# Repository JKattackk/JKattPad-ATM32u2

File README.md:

# JKattPad-ATM32u2
Custom numpad using ATMega32u2, QMK, and USB-C connectivity

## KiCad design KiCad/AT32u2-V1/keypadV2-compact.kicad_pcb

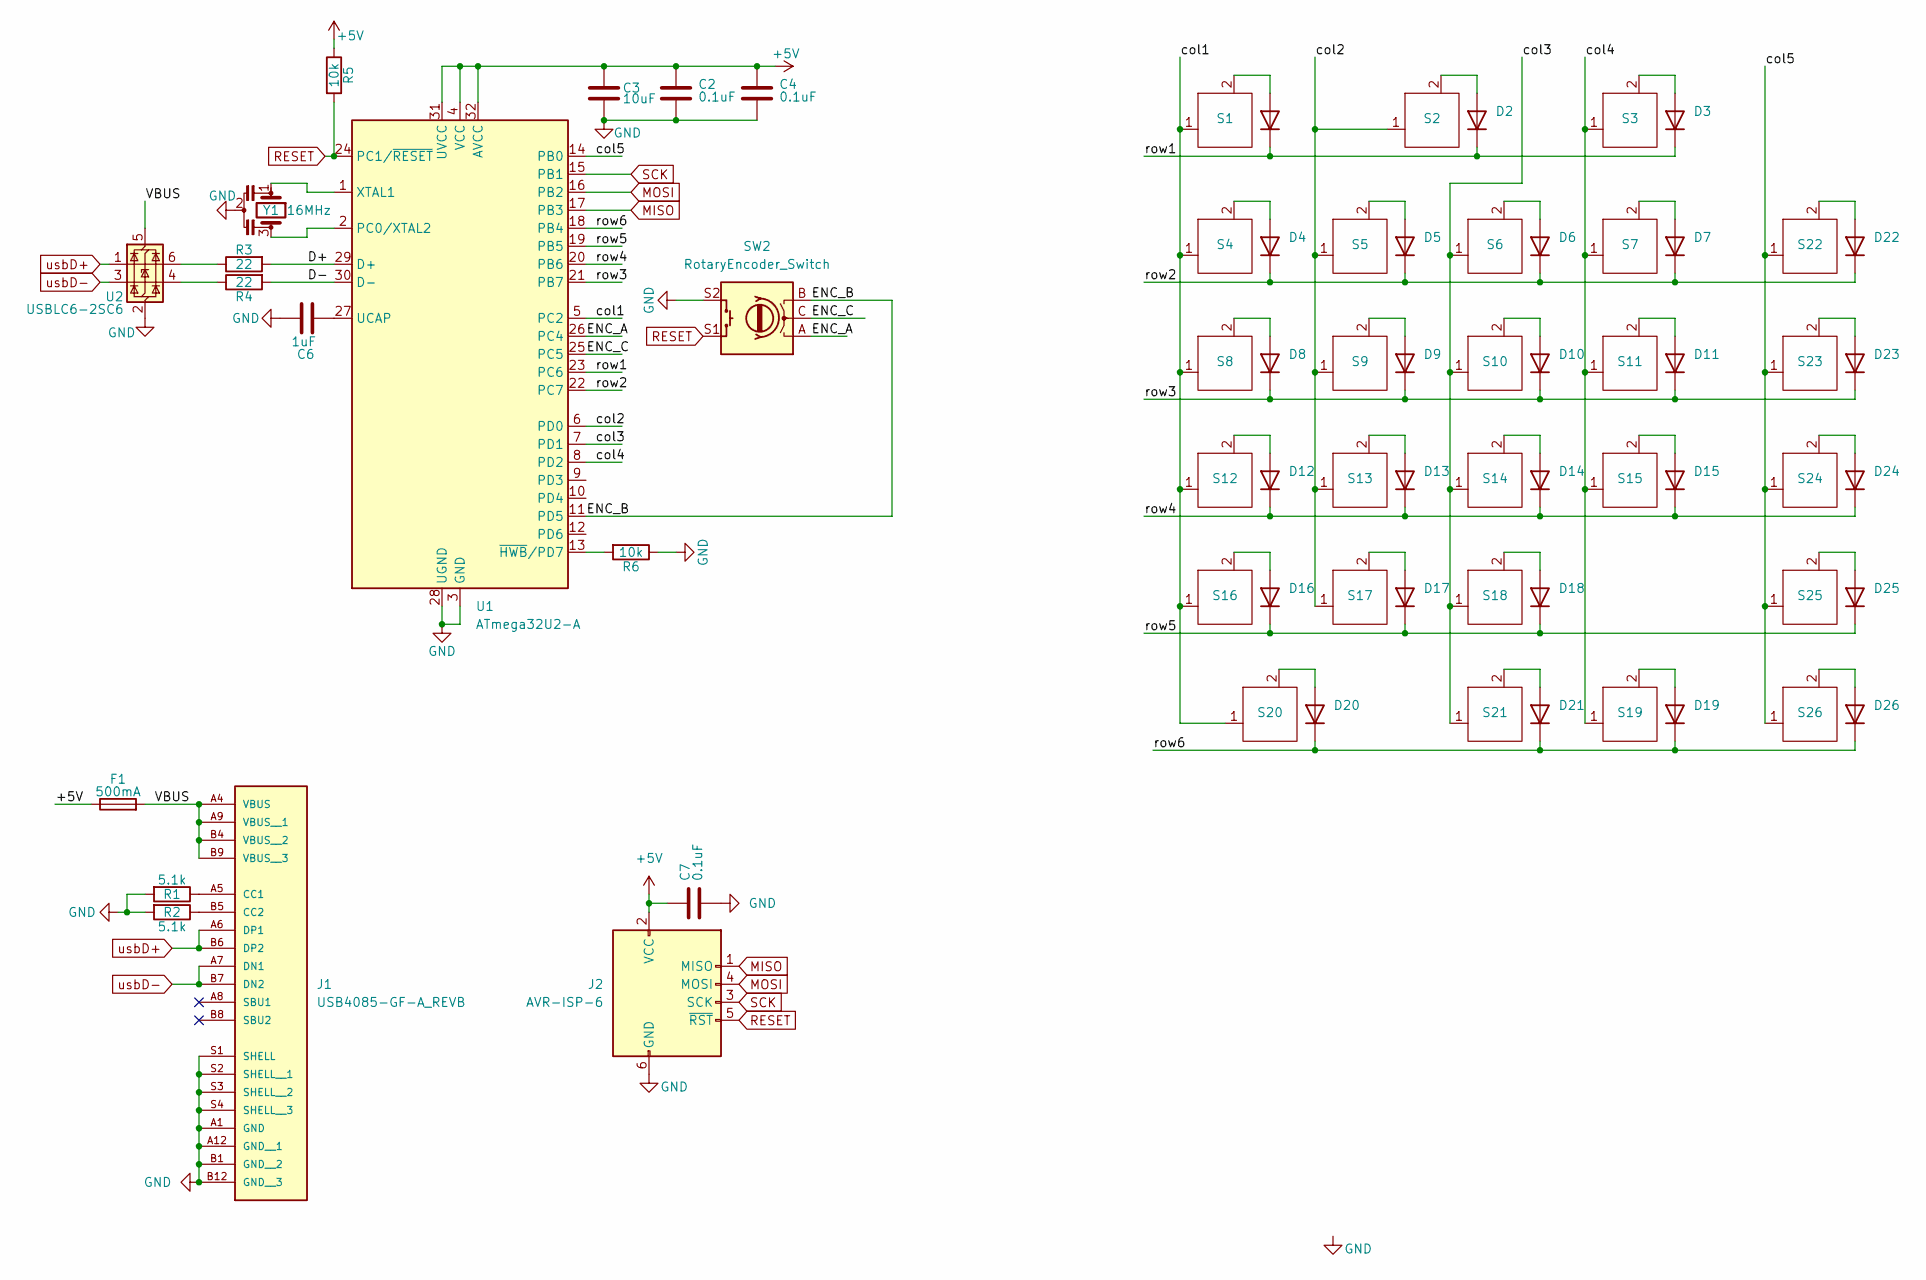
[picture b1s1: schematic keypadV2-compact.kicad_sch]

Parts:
C2, C4, C7: 0.1uF; C_0805_2012Metric_Pad1.18x1.45mm_HandSolder
C3: 10uF; C_0805_2012Metric_Pad1.18x1.45mm_HandSolder
C6: 1uF; C_0805_2012Metric_Pad1.18x1.45mm_HandSolder
D1, D2, D3, D4, D5, D6, D7, D8, D9, D10, D11, D12, D13, D14, D15, D16, D17, D18, D19, D20, D21, D22, D23, D24, D25, D26: BAV16W; D_SOD-123
F1: 500mA; Fuse_0805_2012Metric_Pad1.15x1.40mm_HandSolder
J1: USB4085-GF-A_REVB; GCT_USB4085-GF-A_REVB; PARTREV B
J2: AVR-ISP-6; PinHeader_2x03_P2.54mm_Vertical
R1, R2: 5.1k; R_0805_2012Metric_Pad1.20x1.40mm_HandSolder
R3, R4: 22; R_0805_2012Metric_Pad1.20x1.40mm_HandSolder
R5, R6: 10k; R_0805_2012Metric_Pad1.20x1.40mm_HandSolder
S1, S3, S4, S5, S6, S7, S8, S9, S10, S11, S12, S13, S14, S15, S16, S17, S18, S21, S22, S23, S24, S25, S26: MX-Alps-Hybrid-1U
S2, S20: MX-Alps-Hybrid-2U-nostab
S19: MX-Alps-Hybrid-2U-Vertical-nostab
SW2: RotaryEncoder_Switch; RotaryEncoder_Alps_EC11E-Switch_Vertical_H20mm
U1: ATmega32U2-A; TQFP-32_7x7mm_P0.8mm
U2: USBLC6-2SC6; SOT-23-6_Handsoldering
Y1: 16MHz; Resonator_SMD_Murata_CSTxExxV-3Pin_3.0x1.1mm_HandSoldering

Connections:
+5V: C2.1, C3.1, C4.1, C7.1, F1.1, J2.2 (VCC), R5.1, U1.4 (VCC), U1.31 (UVCC), U1.32 (AVCC)
/D+: R3.2, U1.29 (D+)
/D-: R4.2, U1.30 (D-)
/ENC_A: SW2.A, U1.26 (PC4)
/ENC_B: SW2.B, U1.11 (PD5)
/ENC_C: SW2.C, U1.25 (PC5)
/VBUS: F1.2, J1.A4 (VBUS), J1.A9 (VBUS__1), J1.B4 (VBUS__2), J1.B9 (VBUS__3), U2.5 (VBUS)
/col1: S1.1, S4.1, S8.1, S12.1, S16.1, S20.1, U1.5 (PC2)
/col2: S2.1, S5.1, S9.1, S13.1, S17.1, U1.6 (PD0)
/col3: S6.1, S10.1, S14.1, S18.1, S21.1, U1.7 (PD1)
/col4: S3.1, S7.1, S11.1, S15.1, S19.1, U1.8 (PD2)
/col5: S22.1, S23.1, S24.1, S25.1, S26.1, U1.14 (PB0)
/row1: D1.1 (K), D2.1 (K), D3.1 (K), U1.23 (PC6)
/row2: D4.1 (K), D5.1 (K), D6.1 (K), D7.1 (K), D22.1 (K), U1.22 (PC7)
/row3: D8.1 (K), D9.1 (K), D10.1 (K), D11.1 (K), D23.1 (K), U1.21 (PB7)
/row4: D12.1 (K), D13.1 (K), D14.1 (K), D15.1 (K), D24.1 (K), U1.20 (PB6)
/row5: D16.1 (K), D17.1 (K), D18.1 (K), D25.1 (K), U1.19 (PB5)
/row6: D19.1 (K), D20.1 (K), D21.1 (K), D26.1 (K), U1.18 (PB4)
GND: C2.2, C3.2, C4.2, C6.2, C7.2, J1.A1 (GND), J1.A12 (GND__1), J1.B1 (GND__2), J1.B12 (GND__3), J1.S1 (SHELL), J1.S2 (SHELL__1), J1.S3 (SHELL__2), J1.S4 (SHELL__3), J2.6 (GND), R1.2, R2.2, R6.1, SW2.S2, U1.3 (GND), U1.28 (UGND), U2.2 (GND), Y1.2
MISO: J2.1 (MISO), U1.17 (PB3)
MOSI: J2.4 (MOSI), U1.16 (PB2)
unnamed: D1.2 (A), S1.2
unnamed: D2.2 (A), S2.2
unnamed: D3.2 (A), S3.2
unnamed: D4.2 (A), S4.2
unnamed: D5.2 (A), S5.2
unnamed: D6.2 (A), S6.2
unnamed: D7.2 (A), S7.2
unnamed: D8.2 (A), S8.2
unnamed: D9.2 (A), S9.2
unnamed: D10.2 (A), S10.2
unnamed: D11.2 (A), S11.2
unnamed: D12.2 (A), S12.2
unnamed: D13.2 (A), S13.2
unnamed: D14.2 (A), S14.2
unnamed: D15.2 (A), S15.2
unnamed: D16.2 (A), S16.2
unnamed: D17.2 (A), S17.2
unnamed: D18.2 (A), S18.2
unnamed: D19.2 (A), S19.2
unnamed: D20.2 (A), S20.2
unnamed: D21.2 (A), S21.2
unnamed: D22.2 (A), S22.2
unnamed: D23.2 (A), S23.2
unnamed: D24.2 (A), S24.2
unnamed: D25.2 (A), S25.2
unnamed: D26.2 (A), S26.2
unnamed: J1.A5 (CC1), R1.1
unnamed: J1.B5 (CC2), R2.1
unnamed: R3.1, U2.6 (I/O1)
unnamed: R4.1, U2.4 (I/O2)
unnamed: U1.2 (PC0/XTAL2), Y1.3
unnamed: C6.1, U1.27 (UCAP)
unnamed: U1.1 (XTAL1), Y1.1
unnamed: R6.2, U1.13 (~HWB/PD7)
RESET: J2.5 (~RST), R5.2, SW2.S1, U1.24 (PC1/~RESET)
SCK: J2.3 (SCK), U1.15 (PB1)
usbD+: J1.A6 (DP1), J1.B6 (DP2), U2.1 (I/O1)
usbD-: J1.A7 (DN1), J1.B7 (DN2), U2.3 (I/O2)

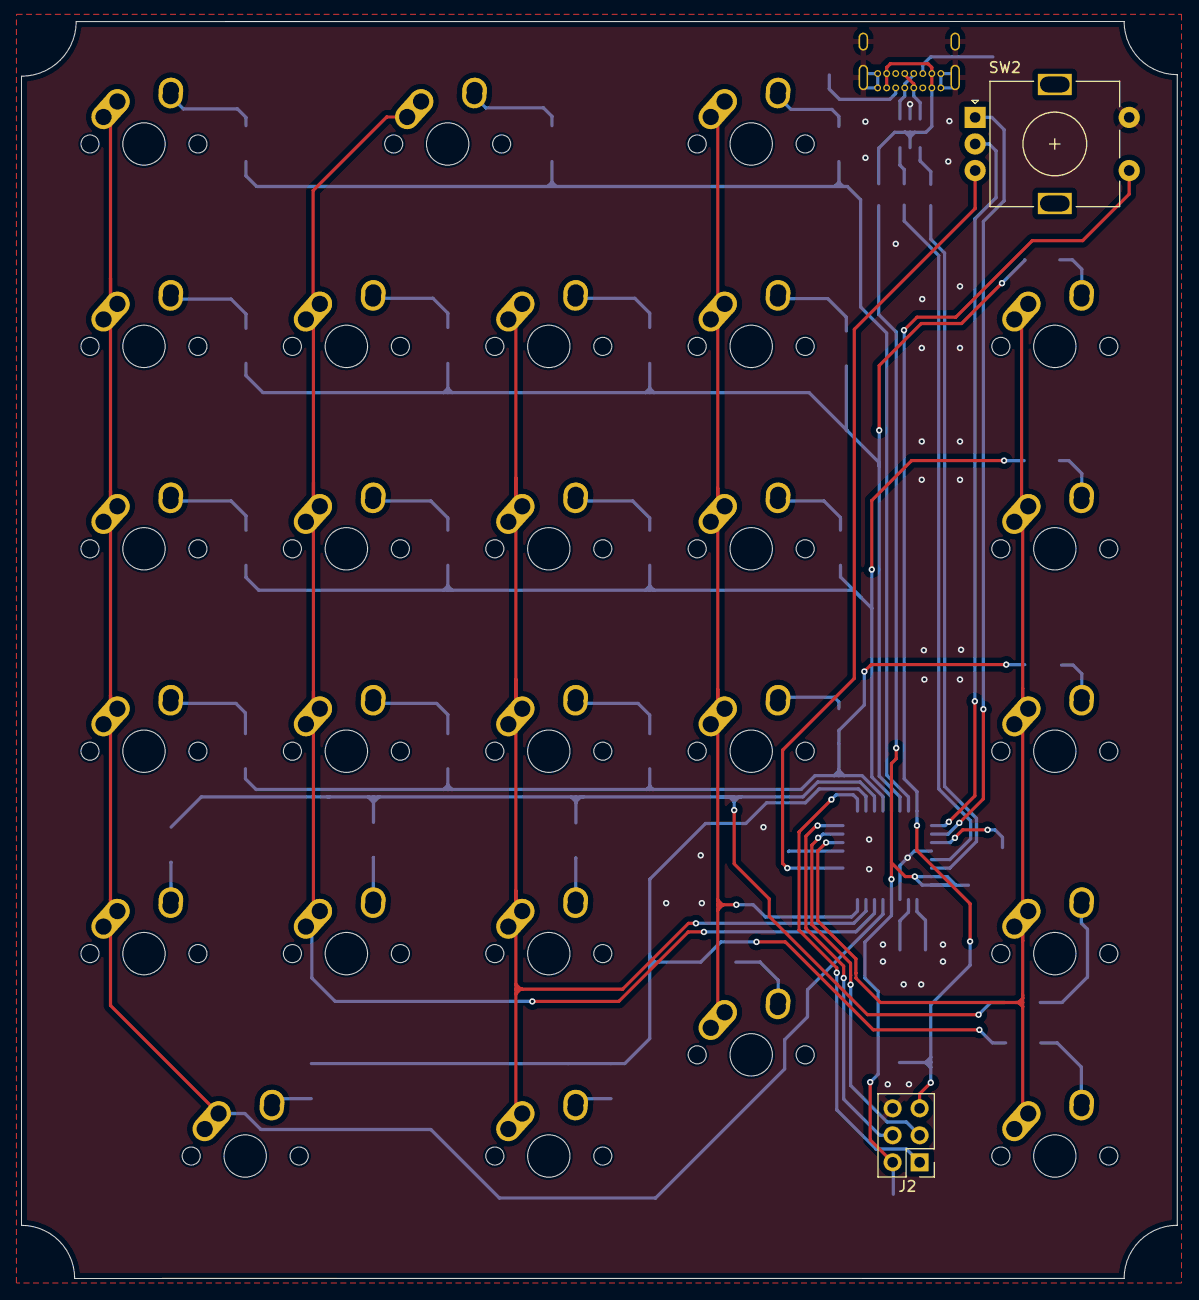
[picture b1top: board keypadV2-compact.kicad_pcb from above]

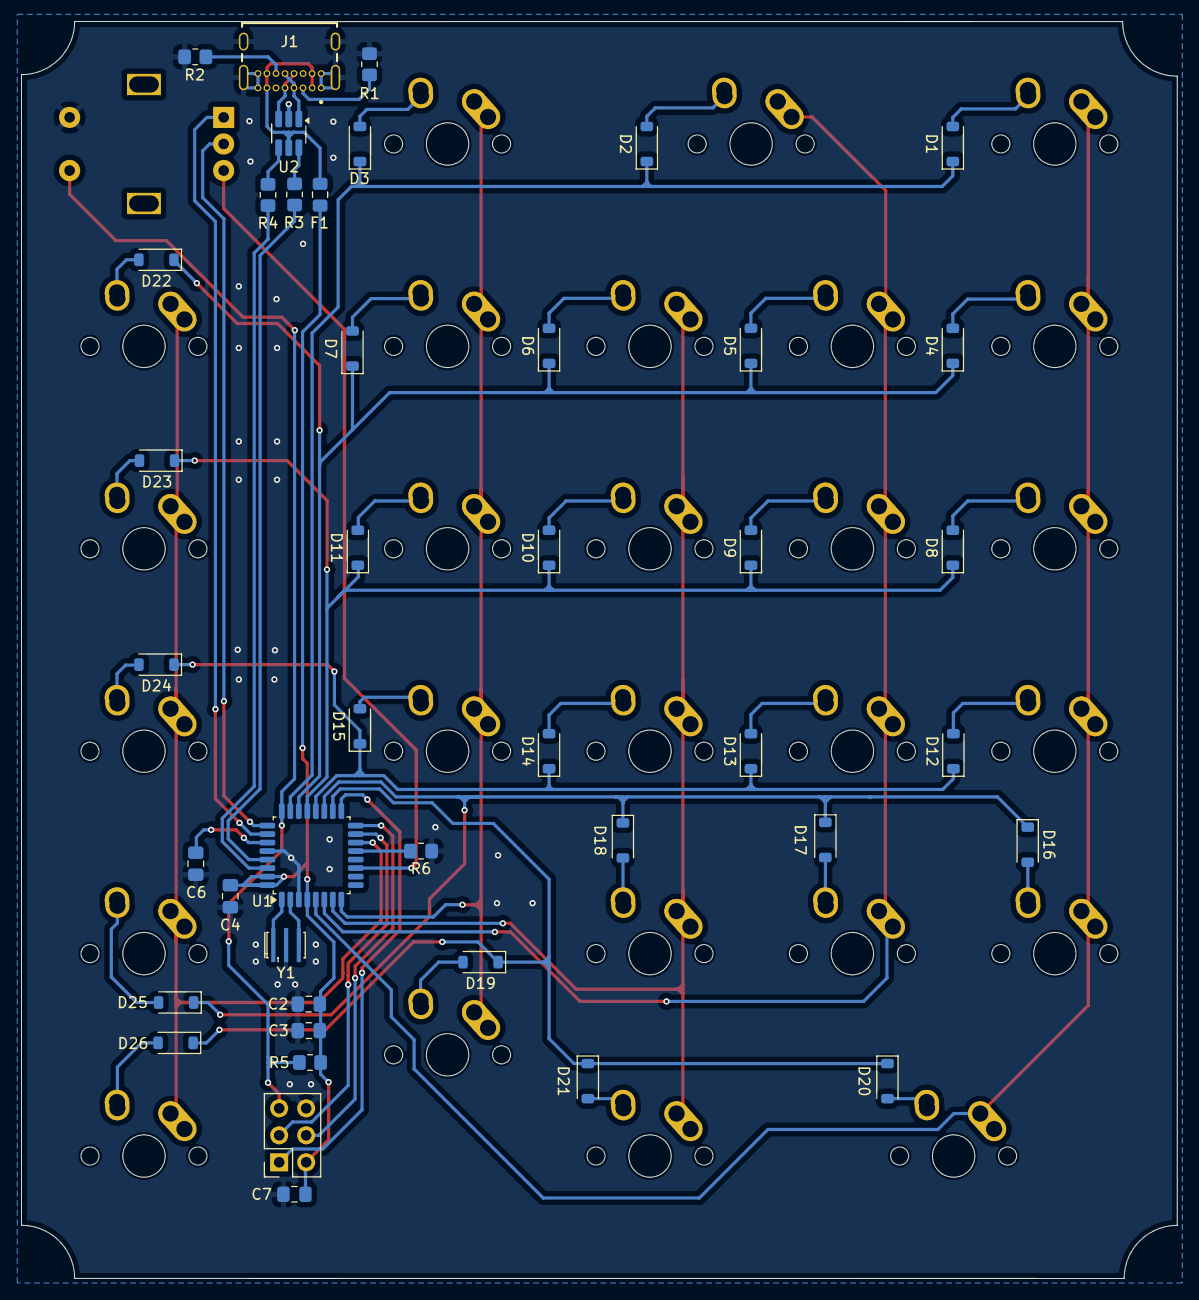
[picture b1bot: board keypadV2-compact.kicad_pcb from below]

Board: 2 copper layers, 108.8 x 118.3 mm, 70 parts (42 on the bottom side), 59 nets.

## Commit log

2025-09-21 Added PCB files
2025-09-23 kicad files
2025-10-04 Schematic adjustment
2025-10-04 Added QMK files
2025-10-06 Added case models
2025-10-06 added some photos
2026-01-02 schem tweaks
